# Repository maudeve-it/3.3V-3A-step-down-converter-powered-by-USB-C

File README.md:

# A 3.3V/3A step-down converter powered via USB-C
<br>
Without needing to use a USB-C PD controller chip, handling communication over the USB cable, USB-C standard allows to get 5V up to 3A through a hardware availability detection.<br> Here I show a design developed on KiCad and assembled through JLCPCB. It is sinking power from a USB-PD connector and provides 5V and 3.3V up to 3A through a step-down converter.<br>
<br>
Project was developed on KiCad 7<br>
<br>
You can find details about this project on the YouTube video: https://youtu.be/P4Y0VTdbARY
<br>
<br>
<i>
  
_**PLEASE NOTE**_<br>
Seeing the video is strongly suggested.<br>
Project stored here is what developed and tested on YouTube.<br>
Once connected to a USB-C PD source it shows a "transient" for about 12 seconds. Avoiding it, a filtering caoacitor should be added.<br>
Again as shown in the video.<br>
</i>
<br>
<br>

---
---

<br>
<br>
<br>

# Uno stabilizzatore step-down 3.3V/3A alimentato via USB-C

<br>
Senza la necessità di usare un controller chip per USB-C PD, che gestisce la comunicazione sul cavo USB, lo standard USB permette di prelevare 5V fino a 3A controllando la disponibilità via hardware.<br>
Qui mostro un progetto realizzato su KiCad e realizzato attraverso JLCPCB, di alimentatore che preleva corrente una porta USB-PD e fornisce 5V e 3.3V fino a 3A attraverso uno step-down converter.<br>
<br>
Il progetto è stato realizzato su KiCad 7<br>
<br>
Puoi trovare i dettagli sul progetto nel video YouTube: https://youtu.be/P4Y0VTdbARY
<br>
<br>
<i>
  
_**NOTA BENE**_<br>
Vedere il video è fortemente suggerito.<br>
Il progetto archiviato qui è quello sviluppato e testato su YouTube.<br>
Connesso ad una alimentazione USB-C PD, mostra un "transitorio" di circa 12 secondi e per evitarlo si deve aggiungere un condensatore di filtro.<br>
Ancora come mostrato nel video.<br>
</i>

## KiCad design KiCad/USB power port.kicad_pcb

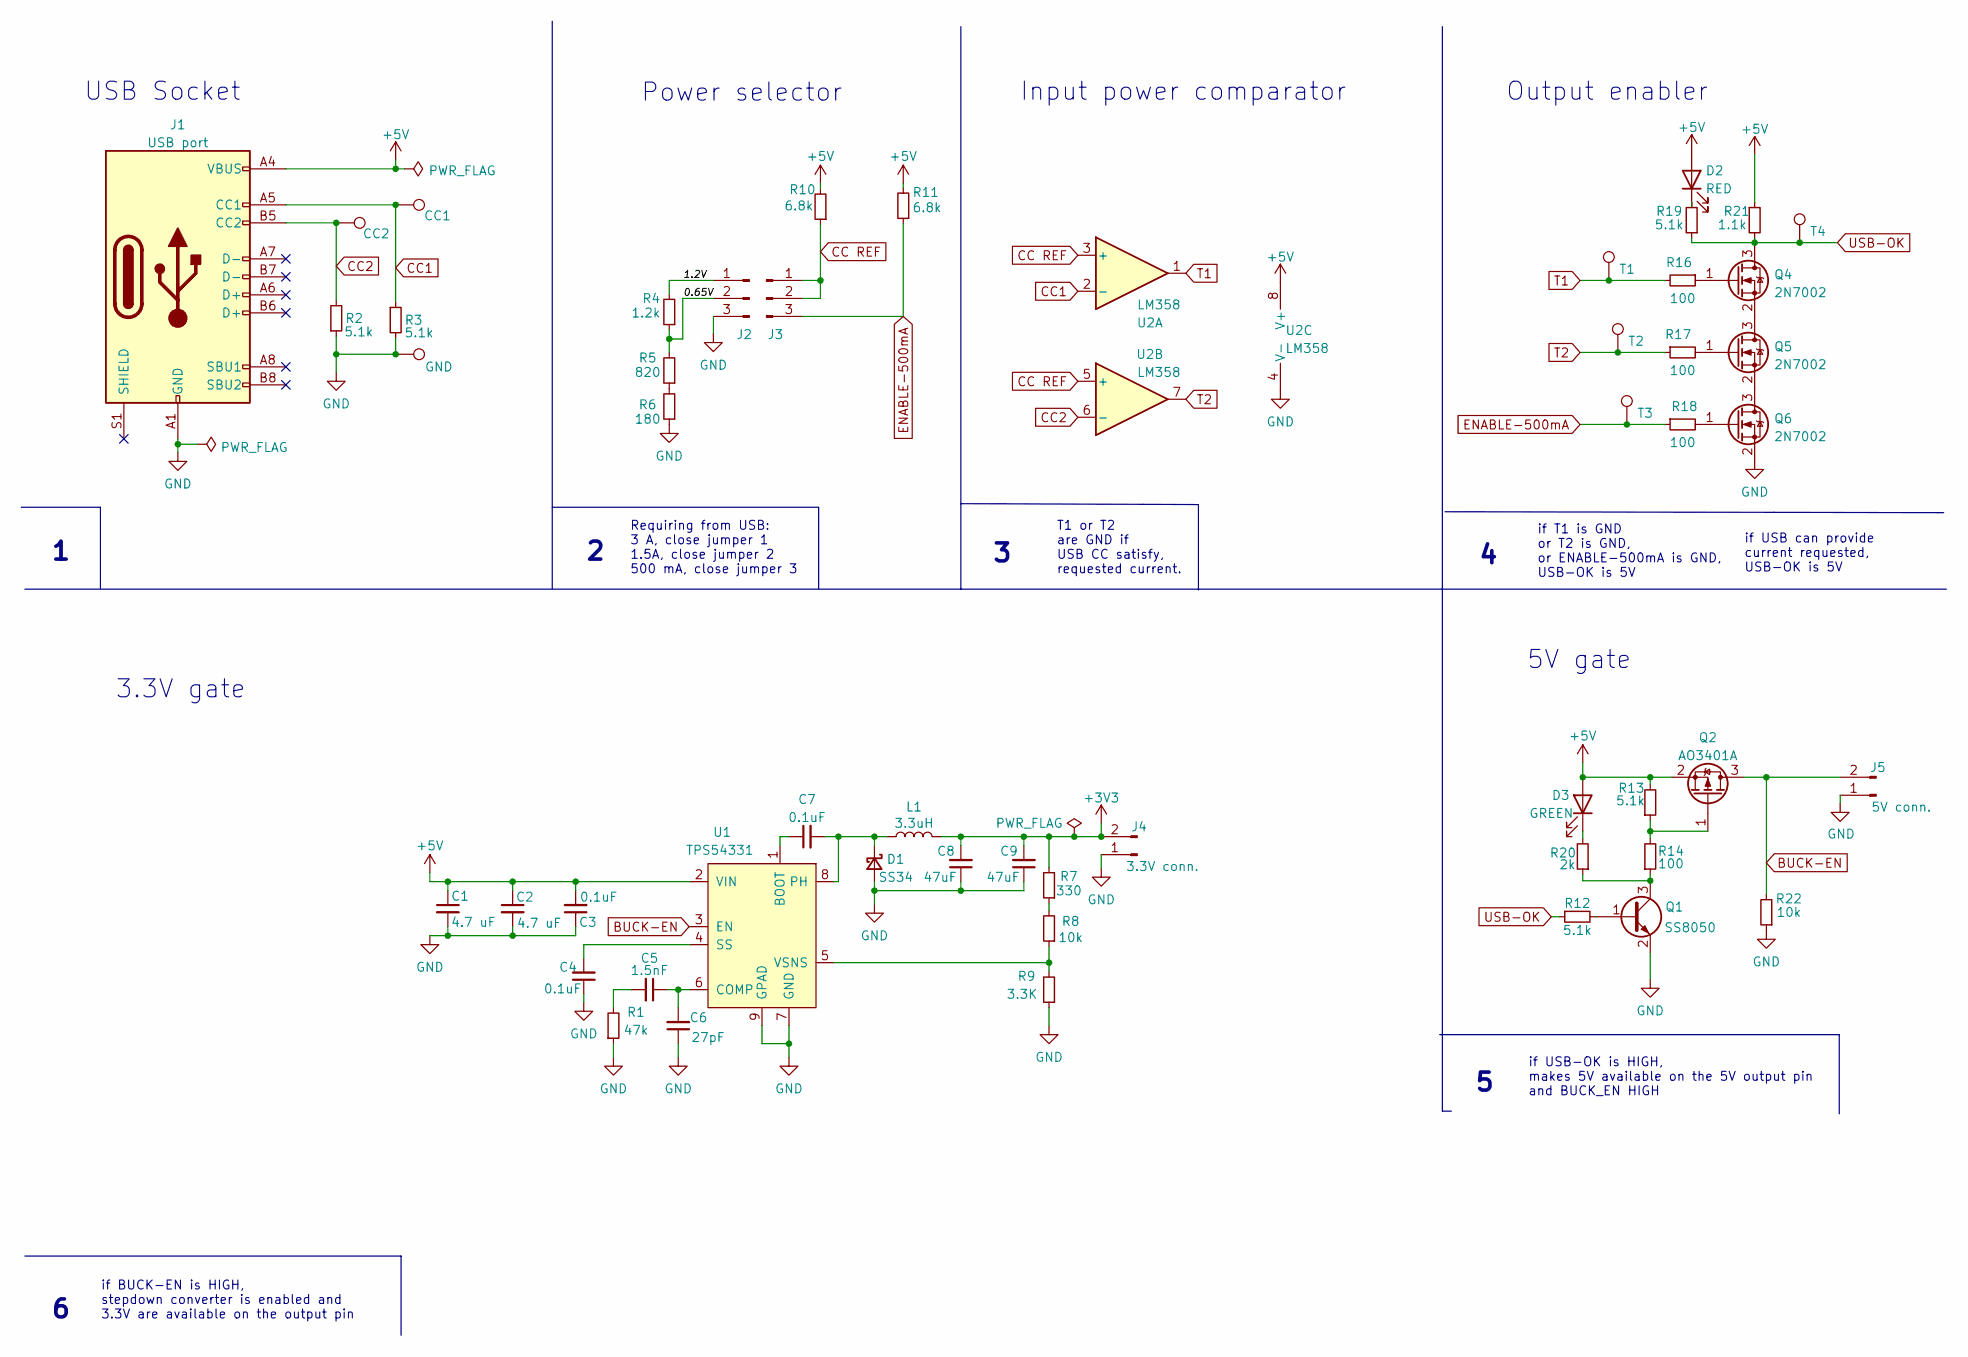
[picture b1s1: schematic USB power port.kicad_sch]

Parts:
C1, C2: 4.7 uF; C_1206_3216Metric; PartNo C29823
C3, C4, C7: 0.1uF; C_0603_1608Metric; PartNo C14663
C5: 1.5nF; C_0603_1608Metric; PartNo C1595
C6: 27pF; C_0603_1608Metric; PartNo C107045
C8, C9: 47uF; C_1206_3216Metric; PartNo C96123
D1: SS34; D_SMA; PartNo C8678
D2: RED; LED_0603_1608Metric; PartNo C2286
D3: GREEN; LED_0603_1608Metric; PartNo C72043
J1: USB port; USB_C_Receptacle_XKB_U262-16XN-4BVC11; PartNo C319148
J2, J3: Selector; PinHeader_1x03_P2.54mm_Vertical
J4: 3.3V conn.; PinHeader_1x02_P2.54mm_Vertical
J5: 5V conn.; PinHeader_1x02_P2.54mm_Vertical
L1: 3.3uH; MWSA0402; PartNo C285742
Q1: SS8050; SOT-23; PartNo C2150
Q2: AO3401A; SOT-23; PartNo C15127
Q4, Q5, Q6: 2N7002; SOT-23; PartNo C8545
R1: 47k; R_0603_1608Metric; PartNo C25819
R2, R3, R12, R13, R19: 5.1k; R_0603_1608Metric; PartNo C23186
R4: 1.2k; R_0603_1608Metric; PartNo C22765
R5: 820; R_0603_1608Metric; PartNo C23253
R6: 180; R_0603_1608Metric; PartNo C22828
R7: 330; R_0603_1608Metric; PartNo C23138
R8, R22: 10k; R_0603_1608Metric; PartNo C25804
R9: 3.3K; R_0603_1608Metric; PartNo C22978
R10, R11: 6.8k; R_0603_1608Metric; PartNo C23212
R14, R16, R17, R18: 100; R_0603_1608Metric; PartNo C22775
R20: 2k; R_0603_1608Metric; PartNo C22975
R21: 1.1k; R_0603_1608Metric; PartNo C22764
TP1: CC2; TestPoint_THTPad_D2.0mm_Drill1.0mm
TP2: CC1; TestPoint_THTPad_D2.0mm_Drill1.0mm
TP3: GND; TestPoint_THTPad_2.0x2.0mm_Drill1.0mm
TP4: T1; TestPoint_THTPad_D2.0mm_Drill1.0mm
TP5: T2; TestPoint_THTPad_D2.0mm_Drill1.0mm
TP6: T3; TestPoint_THTPad_D2.0mm_Drill1.0mm
TP7: T4; TestPoint_THTPad_D2.0mm_Drill1.0mm
U1: TPS54331; TI_SO-PowerPAD-8_ThermalVias; PartNo C9865
U2: LM358; SOIC-8_3.9x4.9mm_P1.27mm; PartNo C7950

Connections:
+3V3: C8.2, C9.2, J4.2, L1.2, R7.2
+5V: C1.1, C2.1, C3.2, D2.2 (A), D3.2 (A), J1.A4 (VBUS), J1.A9 (VBUS), J1.B4 (VBUS), J1.B9 (VBUS), Q2.2 (S), R10.2, R11.2, R13.2, R21.1, U1.2 (VIN), U2.8 (V+)
/0.65V: J2.2, R4.1, R5.2
/1.2V: J2.1, R4.2
BUCK-EN: J5.2, Q2.3 (D), R22.2, U1.3 (EN)
CC1: J1.A5 (CC1), R3.1, TP2.1, U2.2 (-)
CC2: J1.B5 (CC2), R2.2, TP1.1, U2.6 (-)
CC REF: J3.1, J3.2, R10.1, U2.3 (+), U2.5 (+)
ENABLE-500mA: J3.3, R11.1, R18.1, TP6.1
GND: C1.2, C2.2, C3.1, C4.1, C6.1, C8.1, C9.1, D1.2 (A), J1.A1 (GND), J1.A12 (GND), J1.B1 (GND), J1.B12 (GND), J2.3, J4.1, J5.1, Q1.2 (E), Q6.2 (S), R1.1, R2.1, R3.2, R6.1, R9.1, R22.1, TP3.1, U1.7 (GND), U1.9 (GPAD), U2.4 (V-)
unnamed: C5.2, R1.2
unnamed: C7.2, D1.1 (K), L1.1, U1.8 (PH)
unnamed: D2.1 (K), R19.2
unnamed: D3.1 (K), R20.2
unnamed: Q1.1 (B), R12.2
unnamed: Q1.3 (C), R14.1, R20.1
unnamed: Q2.1 (G), R13.1, R14.2
unnamed: Q4.1 (G), R16.1
unnamed: Q4.2 (S), Q5.3 (D)
unnamed: Q5.1 (G), R17.2
unnamed: Q5.2 (S), Q6.3 (D)
unnamed: Q6.1 (G), R18.2
unnamed: R5.1, R6.2
unnamed: R7.1, R8.2
unnamed: C7.1, U1.1 (BOOT)
unnamed: C5.1, C6.2, U1.6 (COMP)
unnamed: C4.2, U1.4 (SS)
unnamed: R8.1, R9.2, U1.5 (VSNS)
T1: R16.2, TP4.1, U2.1
T2: R17.1, TP5.1, U2.7
USB-OK: Q4.3 (D), R12.1, R19.1, R21.2, TP7.1

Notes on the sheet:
Input power comparator
if BUCK-EN is HIGH, stepdown converter is enabled and 3.3V are available on the output pin
if USB-OK is HIGH, makes 5V available on the 5V output pin and BUCK_EN HIGH
USB Socket
Output enabler
if USB can provide current requested, USB-OK is 5V
if T1 is GND or T2 is GND, or ENABLE-500mA is GND, USB-OK is 5V
T1 or T2 are GND if USB CC satisfy, requested current.
Power selector
Requiring from USB: 3 A, close jumper 1 1.5A, close jumper 2 500 mA, close jumper 3
5V gate
3.3V gate

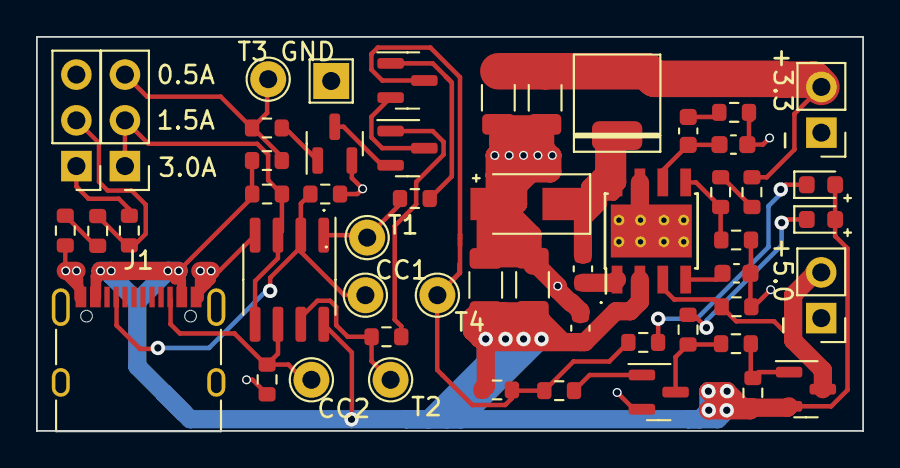
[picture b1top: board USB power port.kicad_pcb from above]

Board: 2 copper layers, 45.9 x 21.9 mm, 53 parts (0 on the bottom side), 31 nets.
